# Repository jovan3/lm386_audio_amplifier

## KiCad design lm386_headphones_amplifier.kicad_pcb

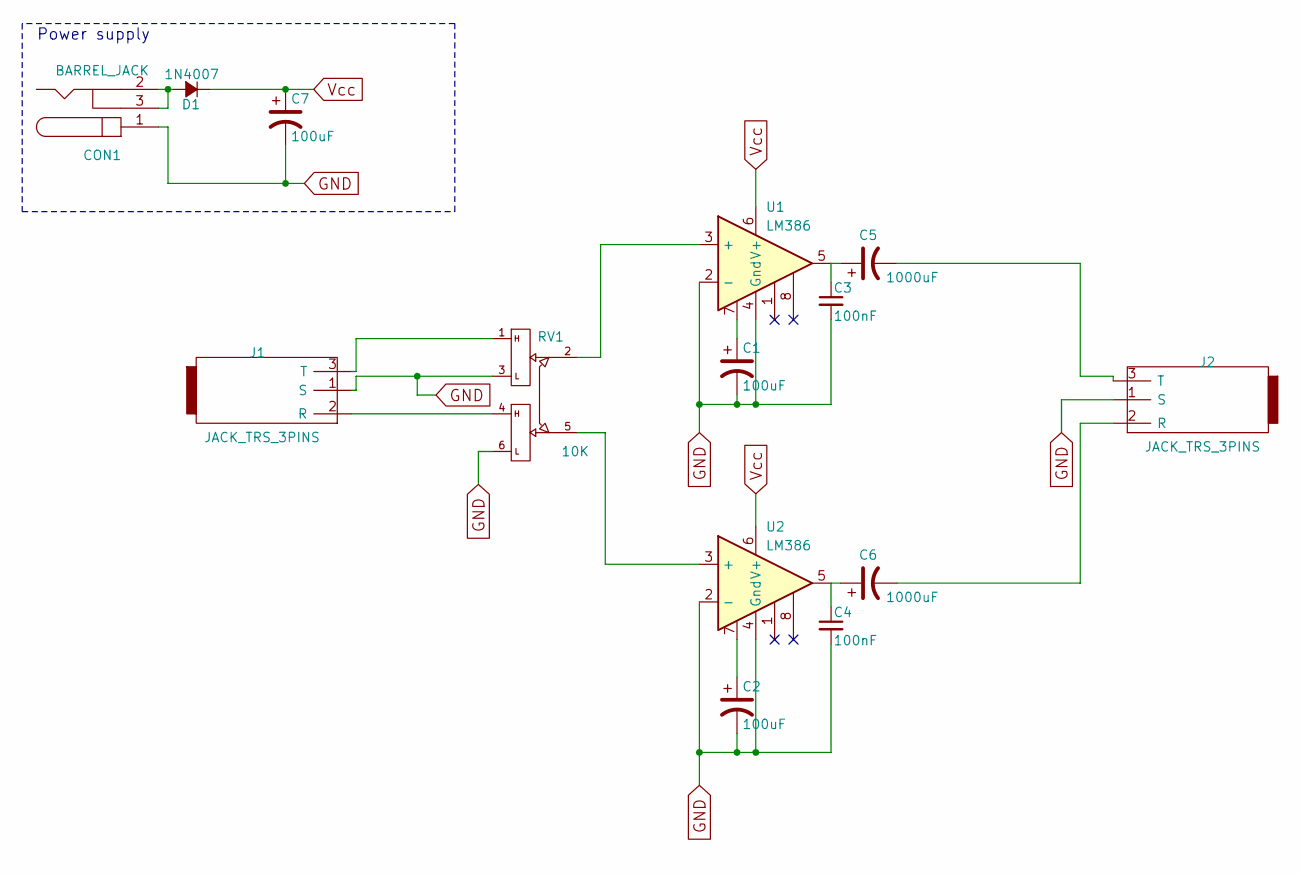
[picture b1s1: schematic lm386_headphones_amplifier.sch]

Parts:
C1, C2, C7: 100uF; C_Radial_D5_L11_P2
C3, C4: 100nF; C_Disc_D3_P2.5
C5, C6: 1000uF; C_Radial_D10_L13_P5
CON1: BARREL_JACK
D1: 1N4007; Diode_DO-35_SOD27_Horizontal_RM10
J1, J2: JACK_TRS_3PINS; 3.5mm_stereo_TRS_jack
RV1: 10K; Potentiometer_Alps-RK16-double
U1, U2: LM386; DIP-8_W7.62mm

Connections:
GND: C1.2, C2.2, C3.2, C4.2, C7.2, CON1.1, J1.1 (S), J2.1 (S), RV1.3, RV1.6, U1.2 (-), U1.4 (Gnd), U2.2 (-), U2.4 (Gnd)
unnamed: C1.1, U1.7
unnamed: C2.1, U2.7
unnamed: C3.1, C5.1, U1.5
unnamed: C4.1, C6.1, U2.5
unnamed: C5.2, J2.3 (T)
unnamed: C6.2, J2.2 (R)
unnamed: CON1.2, CON1.3, D1.2 (A)
unnamed: J1.2 (R), RV1.4
unnamed: J1.3 (T), RV1.1
unnamed: RV1.2, U1.3 (+)
unnamed: RV1.5, U2.3 (+)
Vcc: C7.1, D1.1 (K), U1.6 (V+), U2.6 (V+)

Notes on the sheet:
Power supply

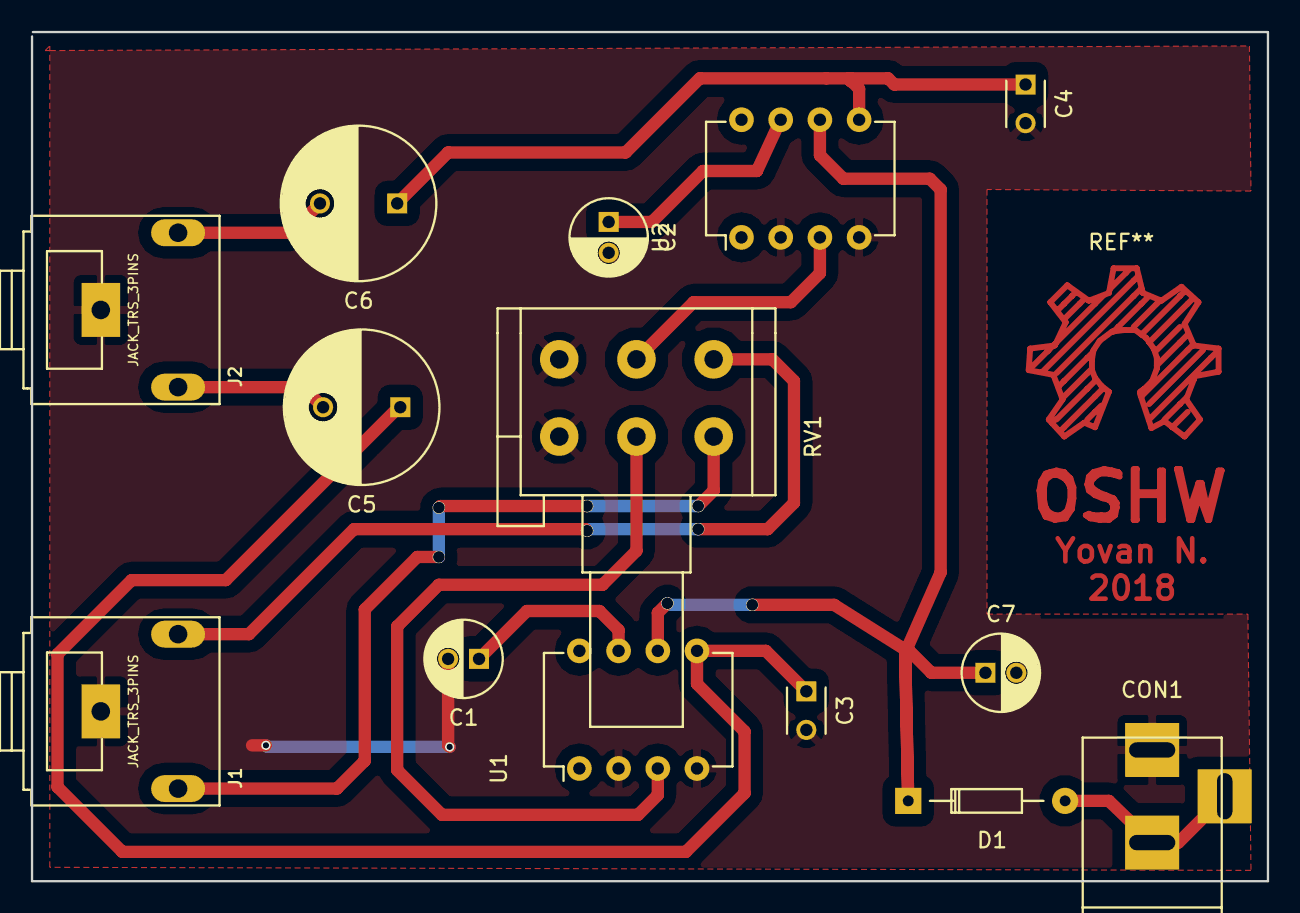
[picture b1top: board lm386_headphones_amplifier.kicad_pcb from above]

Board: 2 copper layers, 80.1 x 55.0 mm, 14 parts (0 on the bottom side), 13 nets.
